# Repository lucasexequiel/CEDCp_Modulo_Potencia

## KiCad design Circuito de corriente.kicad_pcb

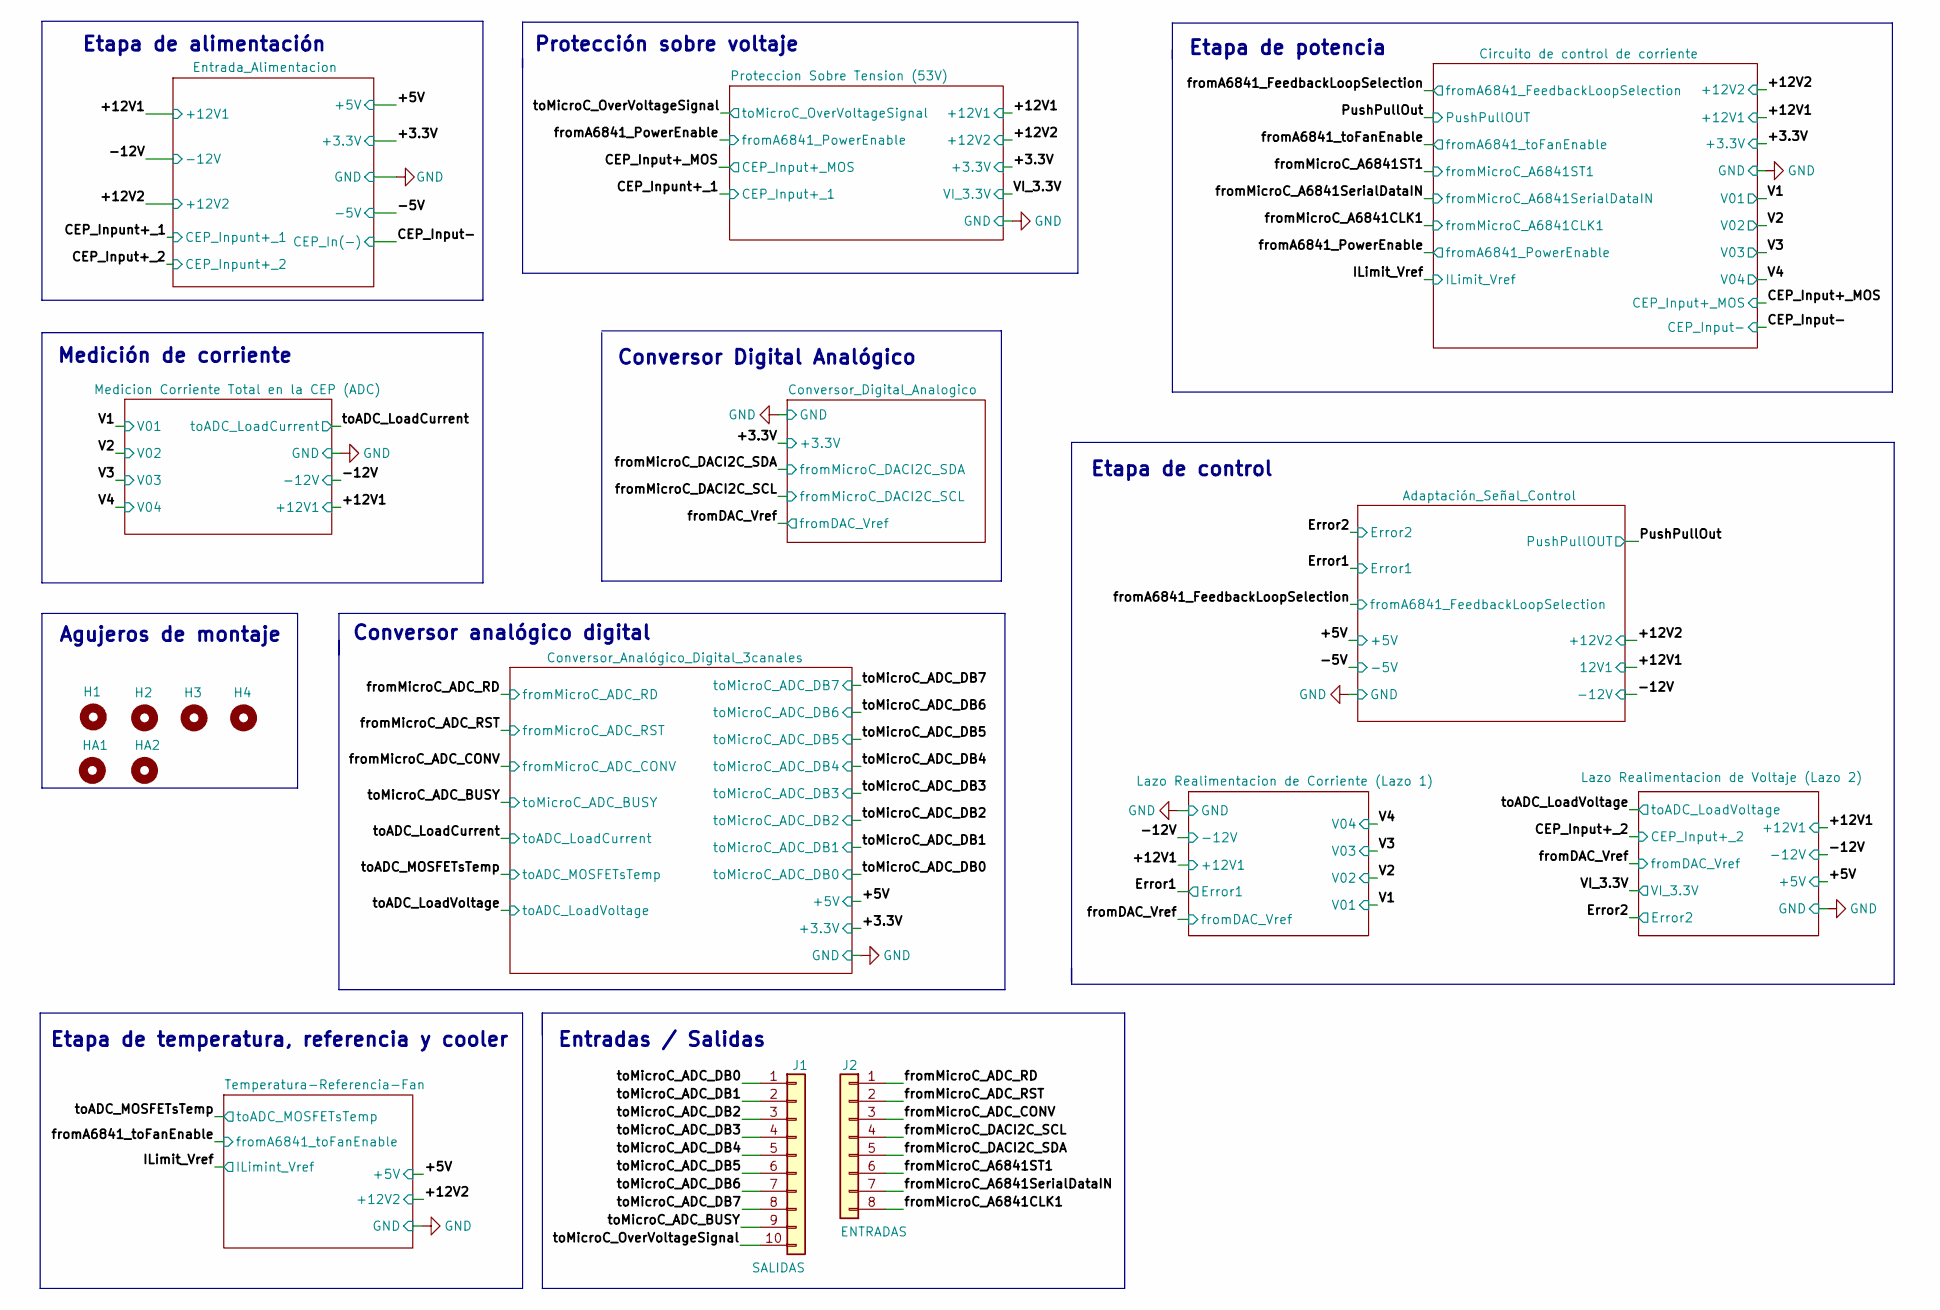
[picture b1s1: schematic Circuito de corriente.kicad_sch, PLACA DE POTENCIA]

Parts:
H1, H2, H3, H4: MountingHole; MountingHole_2.2mm_M2_Pad_Via
HA1, HA2: MountingHole; MountingHole_2.2mm_M2_Pad_Via
J1: SALIDAS; PinHeader_1x10_P2.54mm_Vertical
J2: ENTRADAS; PinHeader_1x08_P2.54mm_Vertical

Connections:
/fromMicroC_A6841CLK1: J2.8; also elsewhere on the board
/fromMicroC_A6841ST1: J2.6; also elsewhere on the board
/fromMicroC_A6841SerialDataIN: J2.7; also elsewhere on the board
/fromMicroC_ADC_CONV: J2.3; also elsewhere on the board
/fromMicroC_ADC_RD: J2.1; also elsewhere on the board
/fromMicroC_ADC_RST: J2.2; also elsewhere on the board
/fromMicroC_DACI2C_SCL: J2.4; also elsewhere on the board
/fromMicroC_DACI2C_SDA: J2.5; also elsewhere on the board
/toMicroC_ADC_BUSY: J1.9; also elsewhere on the board
/toMicroC_ADC_DB0: J1.1; also elsewhere on the board
/toMicroC_ADC_DB1: J1.2; also elsewhere on the board
/toMicroC_ADC_DB2: J1.3; also elsewhere on the board
/toMicroC_ADC_DB3: J1.4; also elsewhere on the board
/toMicroC_ADC_DB4: J1.5; also elsewhere on the board
/toMicroC_ADC_DB5: J1.6; also elsewhere on the board
/toMicroC_ADC_DB6: J1.7; also elsewhere on the board
/toMicroC_ADC_DB7: J1.8; also elsewhere on the board
/toMicroC_OverVoltageSignal: J1.10; also elsewhere on the board

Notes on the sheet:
Etapa de control
Agujeros de montaje
Etapa de temperatura, referencia y cooler
Protección sobre voltaje
Conversor Digital Analógico
Entradas / Salidas
Conversor analógico digital
Medición de corriente
Etapa de potencia
Etapa de alimentación

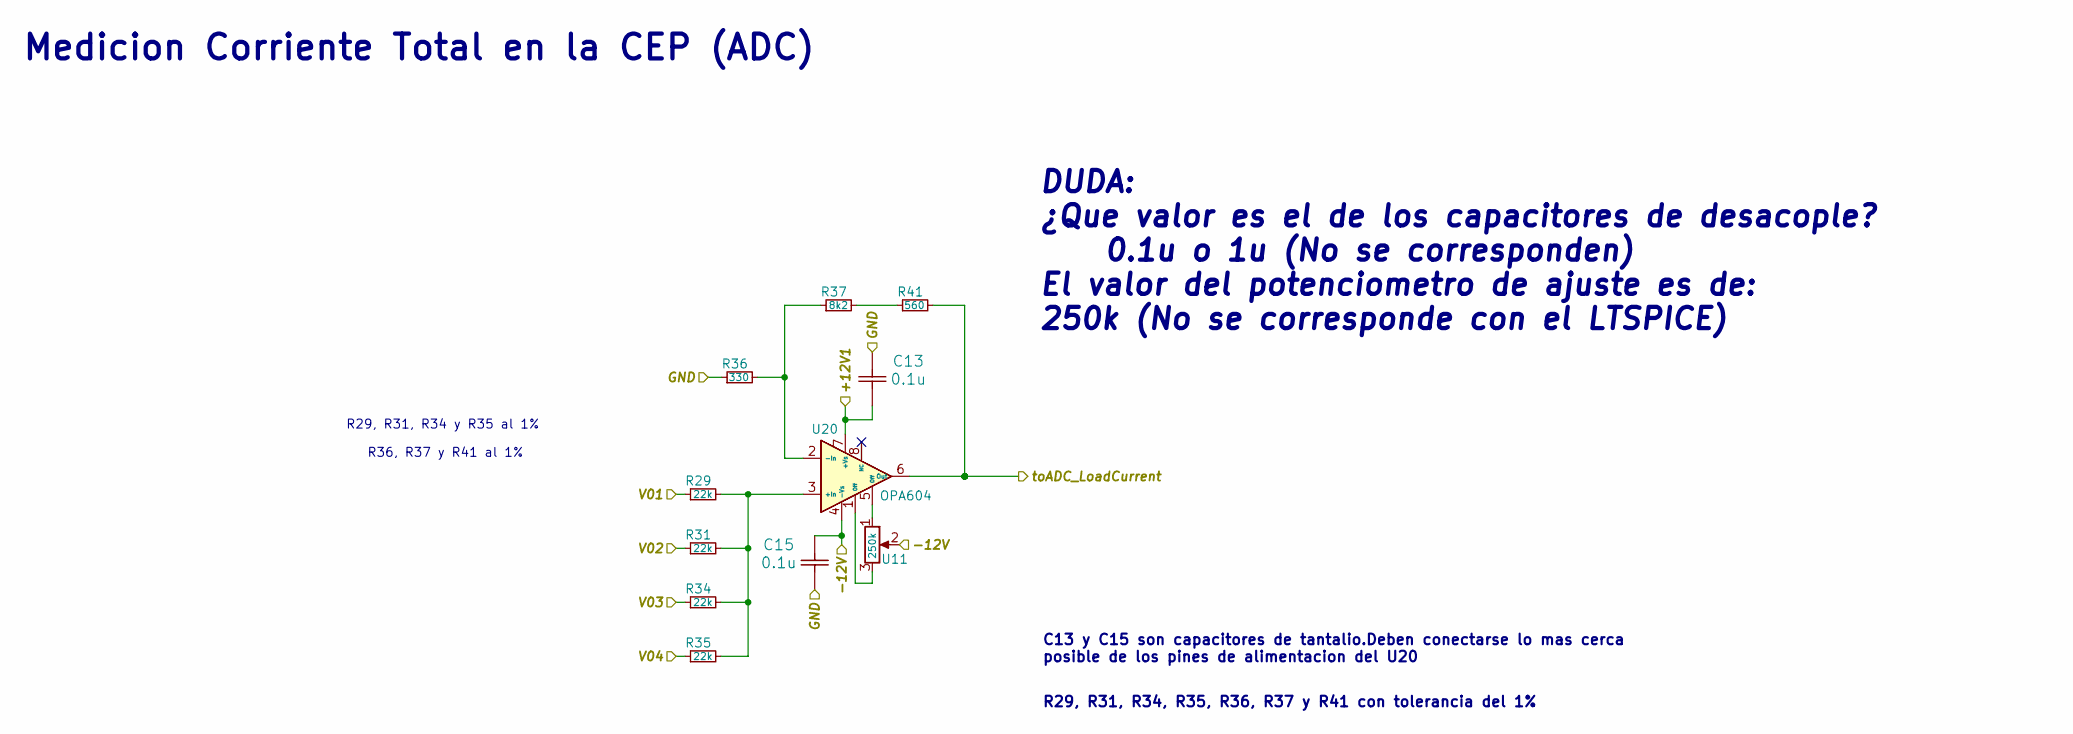
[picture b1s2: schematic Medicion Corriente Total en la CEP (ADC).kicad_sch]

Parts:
C13, C15: 0.1u; C_Disc_D7.5mm_W2.5mm_P5.00mm
R29, R31, R34, R35: 22k; Resistencia_0,25W
R36: 330; Resistencia_0,25W
R37: 8k2; Resistencia_0,25W
R41: 560; Resistencia_0,25W
U11: 250k; Preset_Multivueltas_Vertical
U20: OPA604

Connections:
/+12V1: C13.2, U20.7 (+Vs); also elsewhere on the board
/V1: R29.1; also elsewhere on the board
/V2: R31.1; also elsewhere on the board
/V3: R34.1; also elsewhere on the board
/V4: R35.1; also elsewhere on the board
/toADC_LoadCurrent: R41.2, U20.6 (Out); also elsewhere on the board
GND: C13.1, C15.2, R36.1; also elsewhere on the board
unnamed: R29.2, R31.2, R34.2, R35.2, U20.3 (+In)
unnamed: R36.2, R37.1, U20.2 (-In)
unnamed: R37.2, R41.1

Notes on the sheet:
R29, R31, R34, R35, R36, R37 y R41 con tolerancia del 1%
DUDA: ¿Que valor es el de los capacitores de desacople? 0.1u o 1u (No se corresponden) El valor del potenciometro de ajuste es de: 250k (No se corresponde con el LTSPICE)
R36, R37 y R41 al 1%
Medicion Corriente Total en la CEP (ADC)
C13 y C15 son capacitores de tantalio.Deben conectarse lo mas cerca posible de los pines de alimentacion del U20
R29, R31, R34 y R35 al 1%

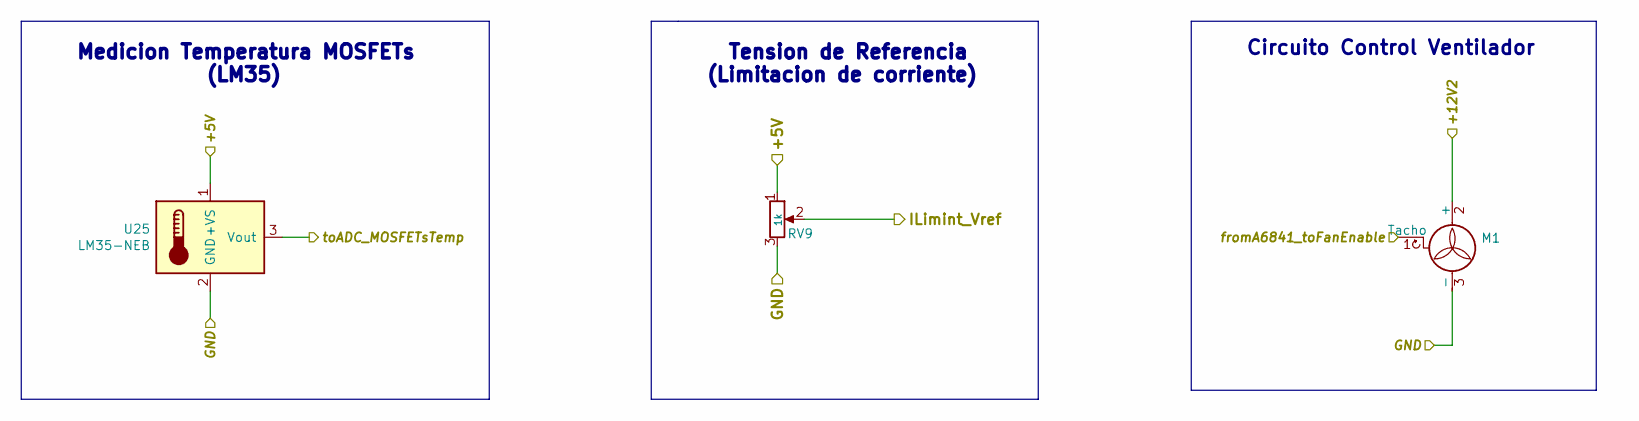
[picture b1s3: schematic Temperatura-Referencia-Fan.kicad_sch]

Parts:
M1: Fan_3pin; PinHeader_1x03_P2.54mm_Vertical
RV9: 1k; Preset_Multivueltas_Vertical
U25: LM35-NEB; PinHeader_1x03_P2.54mm_Vertical

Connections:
/+5V: RV9.1, U25.1 (+VS); also elsewhere on the board
/+12V2: M1.2 (+); also elsewhere on the board
/ILimit_Vref: RV9.2; also elsewhere on the board
/fromA6841_toFanEnable: M1.1 (Tacho); also elsewhere on the board
/toADC_MOSFETsTemp: U25.3 (Vout); also elsewhere on the board
GND: M1.3 (-), RV9.3, U25.2 (GND); also elsewhere on the board

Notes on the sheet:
Tension de Referencia (Limitacion de corriente)
Medicion Temperatura MOSFETs (LM35)
Circuito Control Ventilador

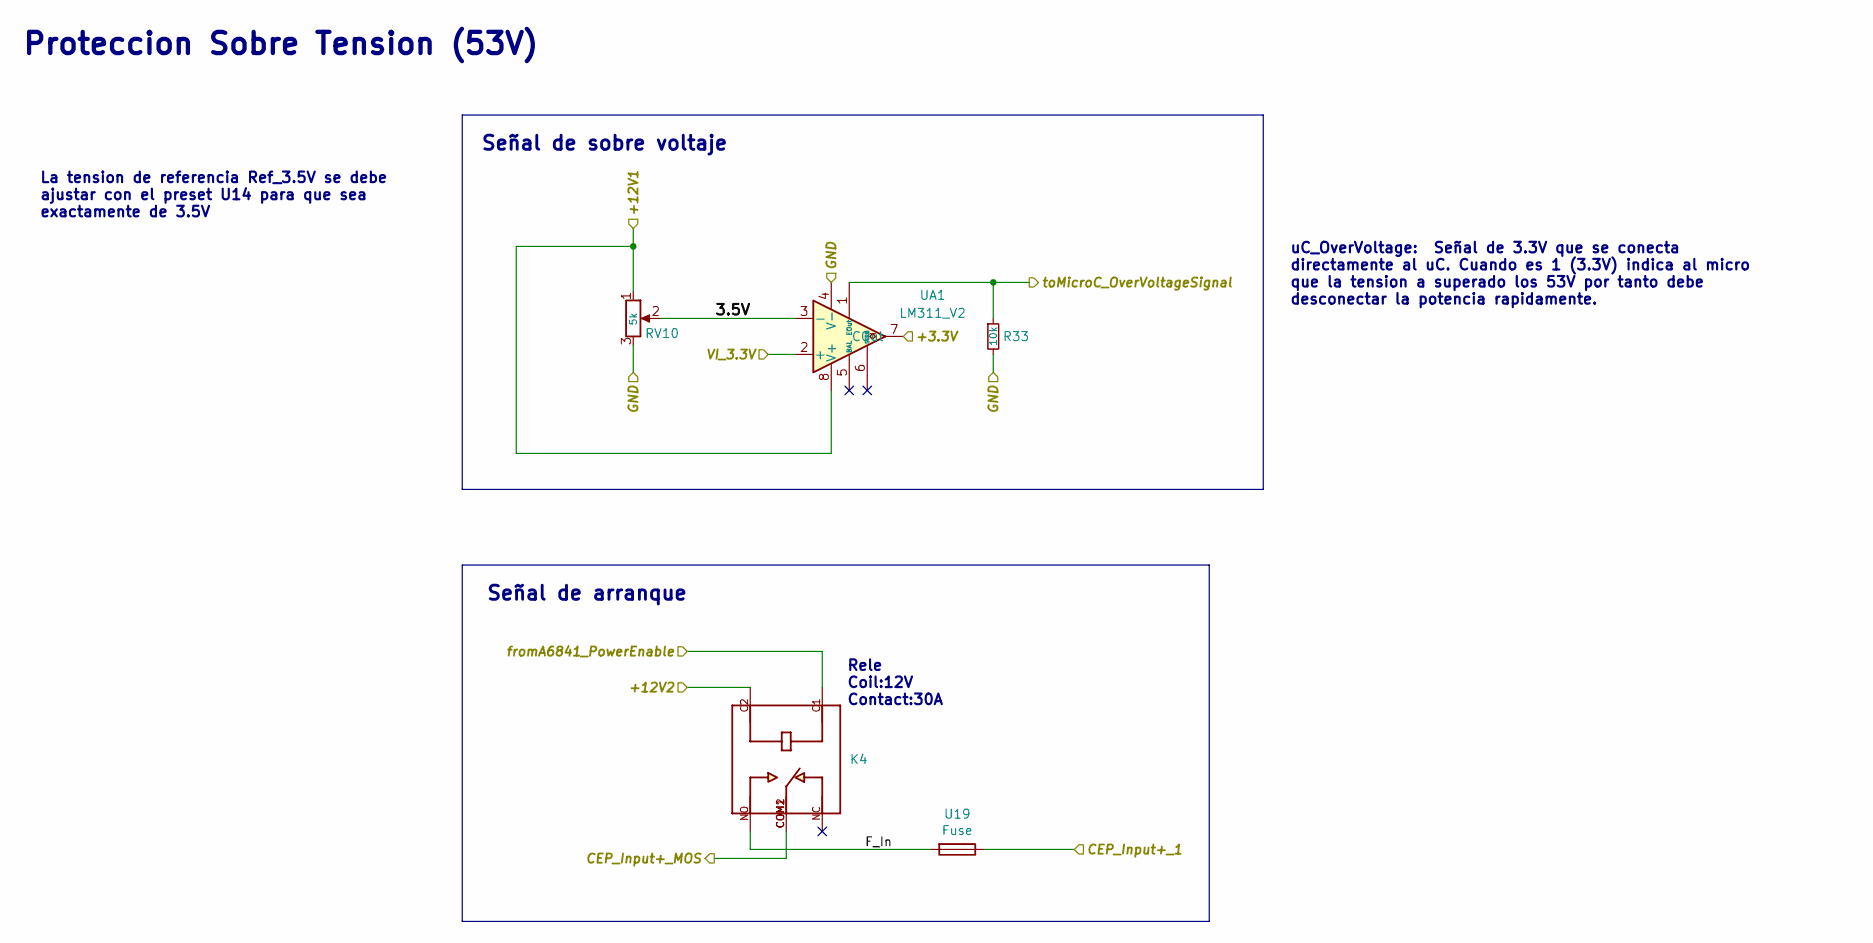
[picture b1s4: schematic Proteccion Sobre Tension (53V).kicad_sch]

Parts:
K4: SLA-12VDC-SL-C; RELE_30A
R33: 10k; Resistencia_0,25W
RV10: 5k; Preset_Multivueltas_Vertical
U19: Fuse
UA1: LM311_V2

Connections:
/+3.3V: UA1.7 (COut); also elsewhere on the board
/+12V1: RV10.1, UA1.8 (V+); also elsewhere on the board
/+12V2: K4.C2; also elsewhere on the board
/CEP_Inpunt+_1: U19.1; also elsewhere on the board
/CEP_Input+_MOS: K4.COM1, K4.COM2; also elsewhere on the board
/Proteccion Sobre Tension (53V)/3.5V: RV10.2, UA1.3 (-)
/Proteccion Sobre Tension (53V)/F_In: K4.NO, U19.2
/VI_3.3V: UA1.2 (+); also elsewhere on the board
/fromA6841_PowerEnable: K4.C1; also elsewhere on the board
/toMicroC_OverVoltageSignal: R33.1, UA1.1 (EOut); also elsewhere on the board
GND: R33.2, RV10.3, UA1.4 (V-); also elsewhere on the board

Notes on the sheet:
Señal de arranque
La tension de referencia Ref_3.5V se debe ajustar con el preset U14 para que sea exactamente de 3.5V
Rele Coil:12V Contact:30A
Proteccion Sobre Tension (53V)
uC_OverVoltage: Señal de 3.3V que se conecta directamente al uC. Cuando es 1 (3.3V) indica al micro que la tension a superado los 53V por tanto debe desconectar la potencia rapidamente.
Señal de sobre voltaje

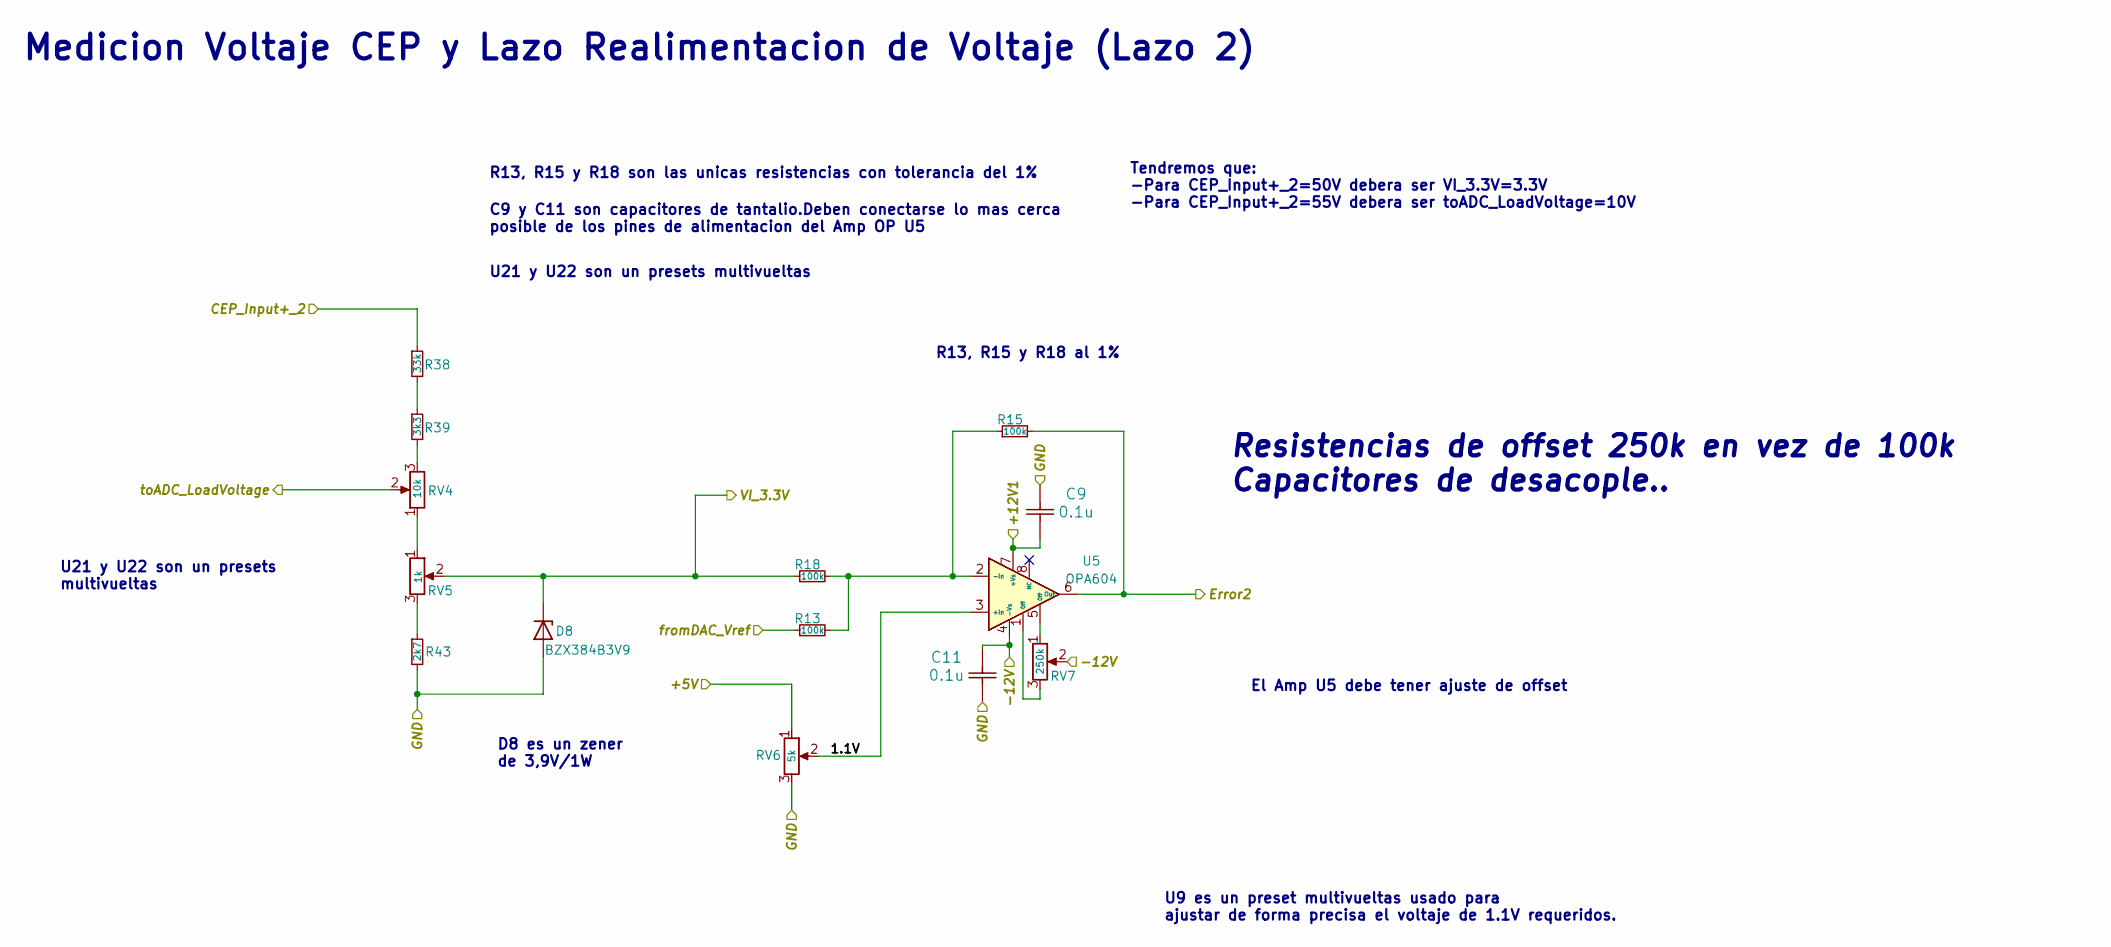
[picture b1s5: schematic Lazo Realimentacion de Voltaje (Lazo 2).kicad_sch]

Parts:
C9, C11: 0.1u; C_Disc_D7.5mm_W2.5mm_P5.00mm
D8: BZX384B3V9; D_DO-15_P10.16mm_Horizontal
R13, R15, R18: 100k; Resistencia_0,25W
R38: 33k; Resistencia_0,25W
R39: 3k3; Resistencia_0,25W
R43: 2k7; Resistencia_0,25W
RV4: 10k; Preset_Multivueltas_Vertical
RV5: 1k; Preset_Multivueltas_Vertical
RV6: 5k; Preset_Multivueltas_Vertical
RV7: 250k; Preset_Multivueltas_Vertical
U5: OPA604

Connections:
/+5V: RV6.1; also elsewhere on the board
/+12V1: C9.2, U5.7 (+Vs); also elsewhere on the board
/CEP_Input+_2: R38.1; also elsewhere on the board
/Error2: R15.2, U5.6 (Out); also elsewhere on the board
/Lazo Realimentacion de Voltaje (Lazo 2)/1.1V: RV6.2, U5.3 (+In)
/VI_3.3V: D8.1 (K), R18.1, RV5.2; also elsewhere on the board
/fromDAC_Vref: R13.1; also elsewhere on the board
/toADC_LoadVoltage: RV4.2; also elsewhere on the board
GND: C9.1, C11.1, D8.2 (A), R43.2, RV6.3; also elsewhere on the board
unnamed: R13.2, R15.1, R18.2, U5.2 (-In)
unnamed: R38.2, R39.1
unnamed: R39.2, RV4.3
unnamed: R43.1, RV5.3
unnamed: RV4.1, RV5.1
unnamed: RV7.1, U5.5 (Off)
unnamed: RV7.3, U5.1 (Off)

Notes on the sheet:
U9 es un preset multivueltas usado para ajustar de forma precisa el voltaje de 1.1V requeridos.
C9 y C11 son capacitores de tantalio.Deben conectarse lo mas cerca posible de los pines de alimentacion del Amp OP U5
El Amp U5 debe tener ajuste de offset
U21 y U22 son un presets multivueltas
D8 es un zener de 3,9V/1W
R13, R15 y R18 al 1%
Resistencias de offset 250k en vez de 100k Capacitores de desacople..
U21 y U22 son un presets multivueltas
Medicion Voltaje CEP y Lazo Realimentacion de Voltaje (Lazo 2)
Tendremos que: -Para CEP_Input+_2=50V debera ser VI_3.3V=3.3V -Para CEP_Input+_2=55V debera ser toADC_LoadVoltage=10V
R13, R15 y R18 son las unicas resistencias con tolerancia del 1%

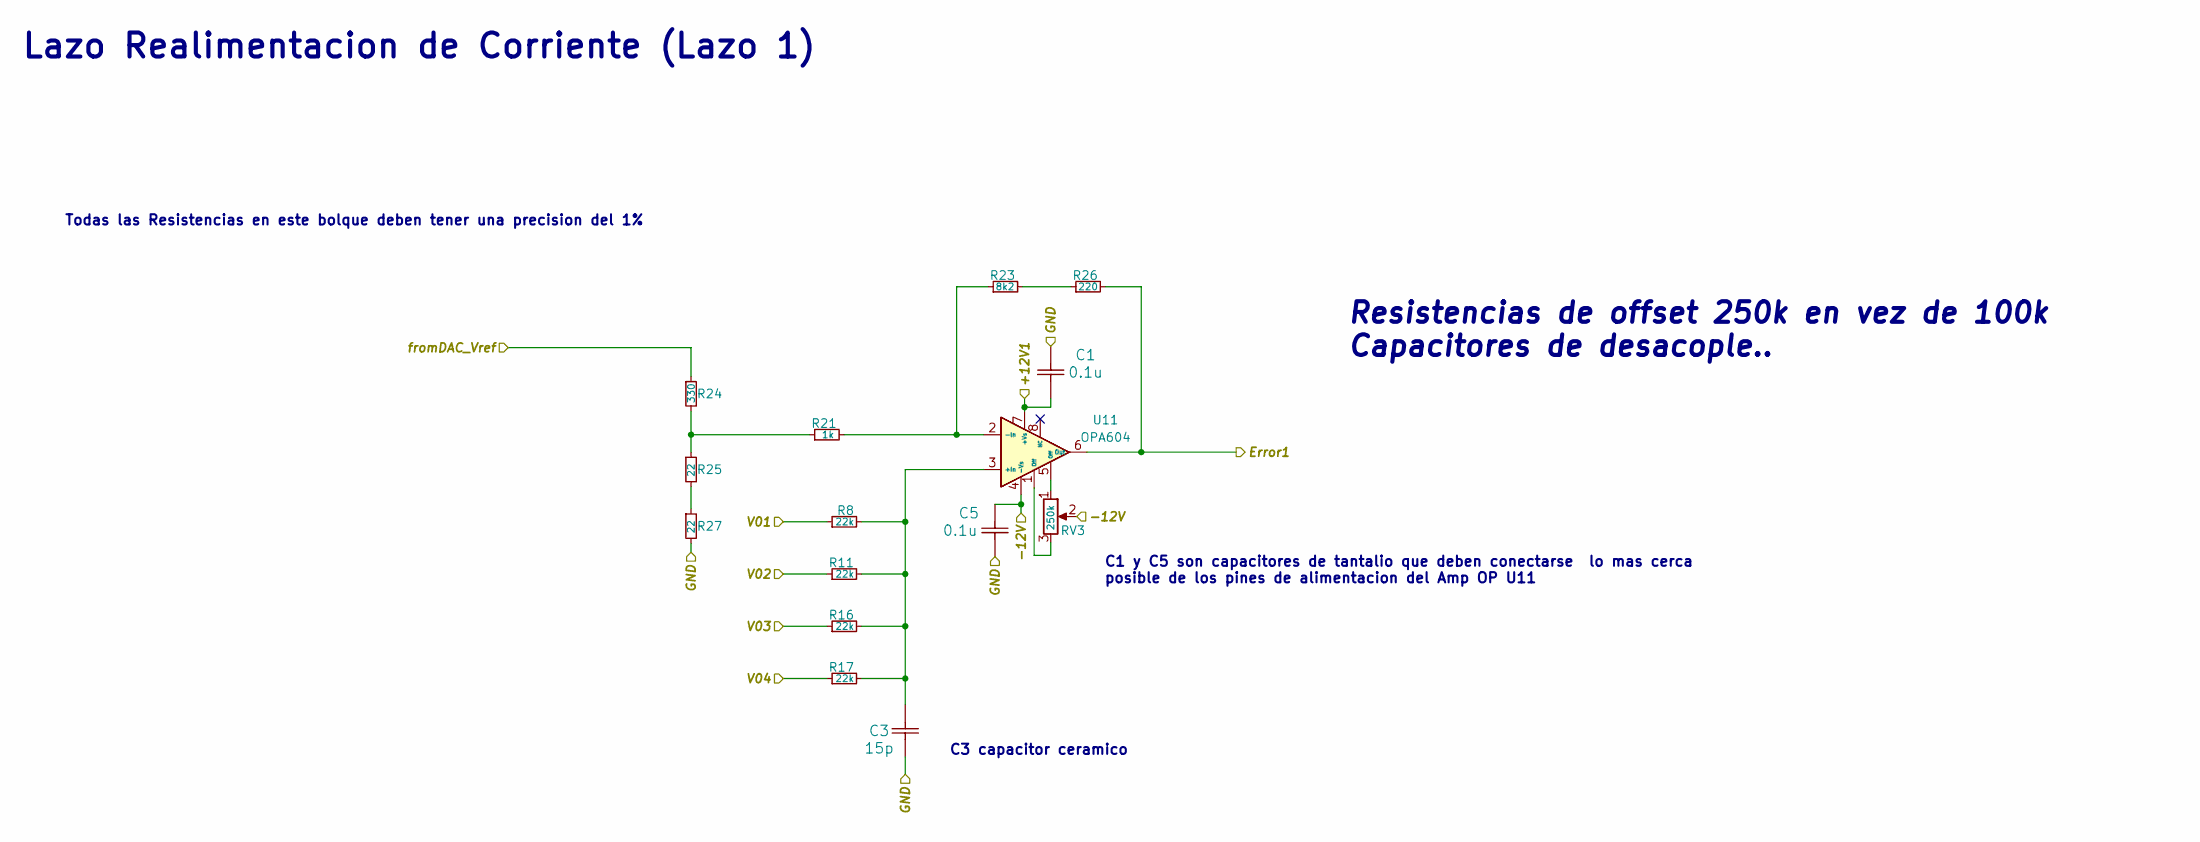
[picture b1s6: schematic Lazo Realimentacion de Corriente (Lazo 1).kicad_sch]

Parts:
C1, C5: 0.1u; C_Disc_D7.5mm_W2.5mm_P5.00mm
C3: 15p; C_Disc_D7.5mm_W2.5mm_P5.00mm
R8, R11, R16, R17: 22k; Resistencia_0,25W
R21: 1k; Resistencia_0,25W
R23: 8k2; Resistencia_0,25W
R24: 330; Resistencia_0,25W
R25, R27: 22; Resistencia_0,25W
R26: 220; Resistencia_0,25W
RV3: 250k; Preset_Multivueltas_Vertical
U11: OPA604

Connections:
/+12V1: C1.2, U11.7 (+Vs); also elsewhere on the board
/Error1: R26.2, U11.6 (Out); also elsewhere on the board
/V1: R8.1; also elsewhere on the board
/V2: R11.1; also elsewhere on the board
/V3: R16.1; also elsewhere on the board
/V4: R17.1; also elsewhere on the board
/fromDAC_Vref: R24.1; also elsewhere on the board
GND: C1.1, C3.1, C5.2, R27.2; also elsewhere on the board
unnamed: R21.1, R24.2, R25.1
unnamed: R23.2, R26.1
unnamed: R25.2, R27.1
unnamed: RV3.1, U11.5 (Off)

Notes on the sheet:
C3 capacitor ceramico
Resistencias de offset 250k en vez de 100k Capacitores de desacople..
Lazo Realimentacion de Corriente (Lazo 1)
Todas las Resistencias en este bolque deben tener una precision del 1%
C1 y C5 son capacitores de tantalio que deben conectarse lo mas cerca posible de los pines de alimentacion del Amp OP U11

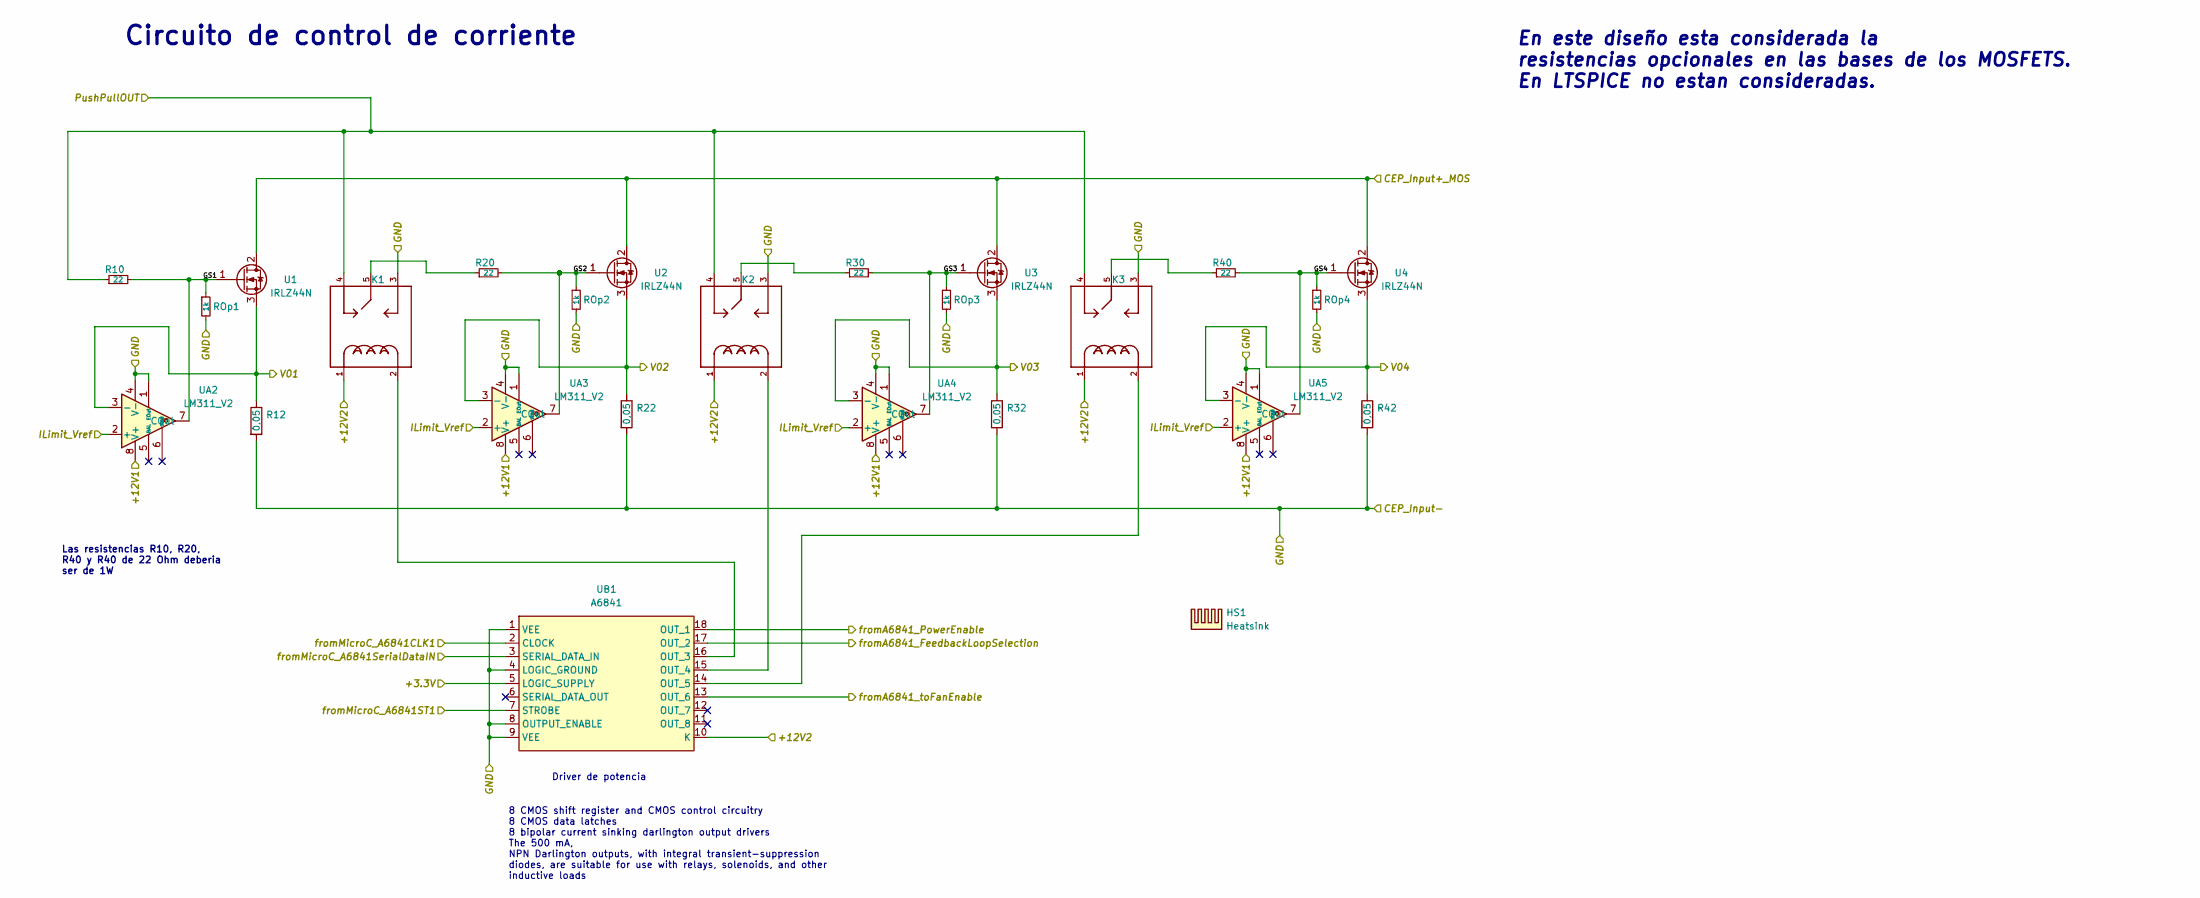
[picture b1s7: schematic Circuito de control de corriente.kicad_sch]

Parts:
HS1: Heatsink; Heatsink_125x35x50mm_3xFixationM3
K1, K2, K3: JJM1-12V; RELAY_JJM1-12V
R10, R20, R30, R40: 22; Resistencia_0,25W
R12, R22, R32, R42: 0,05; C_Rect_L16.5mm_W4.7mm_P15.00mm_MKT
ROp1, ROp2, ROp3, ROp4: 1k; Resistencia_0,25W
U1, U2, U3, U4: IRLZ44N; TO-220-3_Vertical
UA2, UA3, UA4, UA5: LM311_V2
UB1: A6841

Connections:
/+3.3V: UB1.5 (LOGIC_SUPPLY); also elsewhere on the board
/+12V1: UA2.8 (V+), UA3.8 (V+), UA4.8 (V+), UA5.8 (V+); also elsewhere on the board
/+12V2: K1.1, K2.1, K3.1, UB1.10 (K); also elsewhere on the board
/CEP_Input+_MOS: U1.2 (D), U2.2 (D), U3.2 (D), U4.2 (D); also elsewhere on the board
/Circuito de control de corriente/GS1: R10.2, ROp1.1, U1.1 (G), UA2.7 (COut)
/Circuito de control de corriente/GS2: R20.2, ROp2.1, U2.1 (G), UA3.7 (COut)
/Circuito de control de corriente/GS3: R30.2, ROp3.1, U3.1 (G), UA4.7 (COut)
/Circuito de control de corriente/GS4: R40.2, ROp4.1, U4.1 (G), UA5.7 (COut)
/ILimit_Vref: UA2.2 (+), UA3.2 (+), UA4.2 (+), UA5.2 (+); also elsewhere on the board
/PushPullOut: K1.4 (NC), K2.4 (NC), K3.4 (NC), R10.1; also elsewhere on the board
/V1: R12.1, U1.3 (S), UA2.3 (-); also elsewhere on the board
/V2: R22.1, U2.3 (S), UA3.3 (-); also elsewhere on the board
/V3: R32.1, U3.3 (S), UA4.3 (-); also elsewhere on the board
/V4: R42.1, U4.3 (S), UA5.3 (-); also elsewhere on the board
/fromA6841_FeedbackLoopSelection: UB1.17 (OUT_2); also elsewhere on the board
/fromA6841_PowerEnable: UB1.18 (OUT_1); also elsewhere on the board
/fromA6841_toFanEnable: UB1.13 (OUT_6); also elsewhere on the board
/fromMicroC_A6841CLK1: UB1.2 (CLOCK); also elsewhere on the board
/fromMicroC_A6841ST1: UB1.7 (STROBE); also elsewhere on the board
/fromMicroC_A6841SerialDataIN: UB1.3 (SERIAL_DATA_IN); also elsewhere on the board
GND: K1.3 (NO), K2.3 (NO), K3.3 (NO), R12.2, R22.2, R32.2, R42.2, ROp1.2, ROp2.2, ROp3.2, ROp4.2, UA2.1 (EOut), UA2.4 (V-), UA3.1 (EOut), UA3.4 (V-), UA4.1 (EOut), UA4.4 (V-), UA5.1 (EOut), UA5.4 (V-), UB1.1 (VEE), UB1.4 (LOGIC_GROUND), UB1.8 (OUTPUT_ENABLE), UB1.9 (VEE); also elsewhere on the board
unnamed: K1.2, UB1.16 (OUT_3)
unnamed: K1.5 (C), R20.1
unnamed: K2.2, UB1.15 (OUT_4)
unnamed: K2.5 (C), R30.1
unnamed: K3.2, UB1.14 (OUT_5)
unnamed: K3.5 (C), R40.1

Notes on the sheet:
Driver de potencia
8 CMOS shift register and CMOS control circuitry 8 CMOS data latches 8 bipolar current sinking darlington output drivers The 500 mA, NPN Darlington outputs, with integral transient-suppression diodes, are suitable for use with relays, solenoids, and other inductive loads
Circuito de control de corriente
Las resistencias R10, R20, R40 y R40 de 22 Ohm deberia ser de 1W
En este diseño esta considerada la resistencias opcionales en las bases de los MOSFETS. En LTSPICE no estan consideradas.

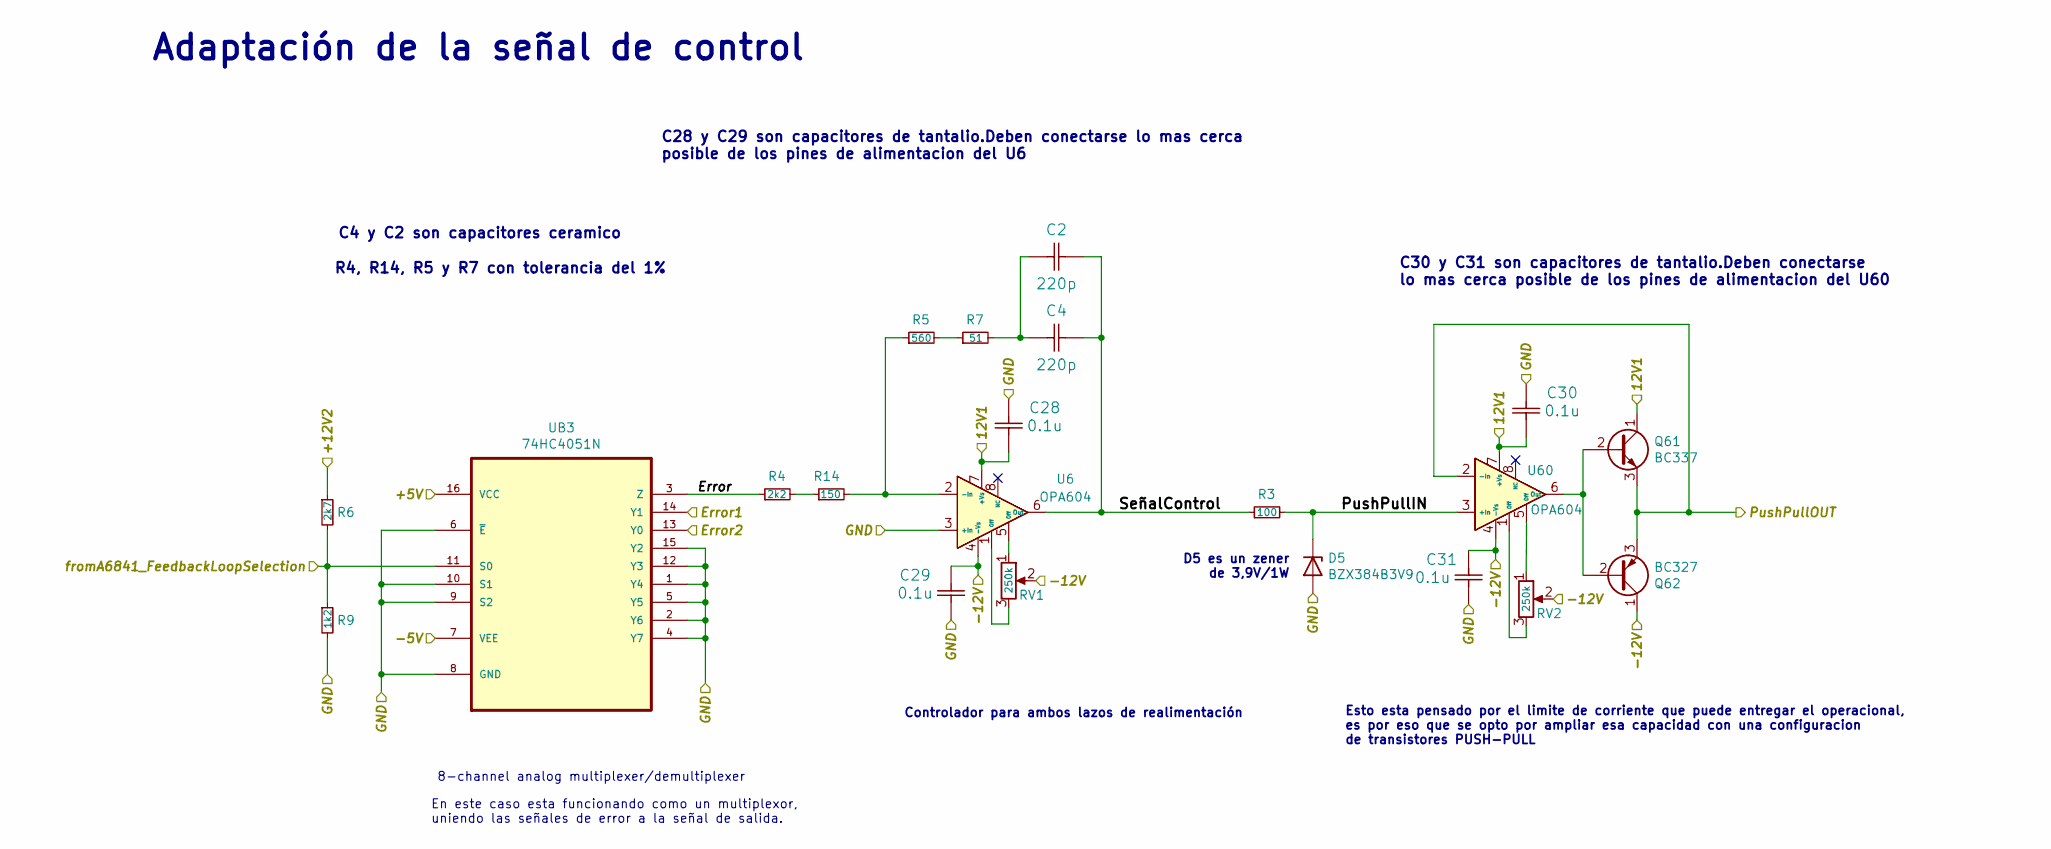
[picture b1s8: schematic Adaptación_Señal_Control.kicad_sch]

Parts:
C2, C4: 220p; C_Disc_D7.5mm_W2.5mm_P5.00mm
C28, C29, C30, C31: 0.1u; C_Disc_D7.5mm_W2.5mm_P5.00mm
D5: BZX384B3V9; D_DO-41_SOD81_P10.16mm_Horizontal
Q61: BC337; TO-92_Inline
Q62: BC327; TO-92_Inline
R3: 100; Resistencia_0,25W
R4: 2k2; Resistencia_0,25W
R5: 560; Resistencia_0,25W
R6: 2k7; Resistencia_0,25W
R7: 51; Resistencia_0,25W
R9: 1k2; Resistencia_0,25W
R14: 150; Resistencia_0,25W
RV1, RV2: 250k; Preset_Multivueltas_Vertical
U6, U60: OPA604
UB3: 74HC4051N; 74HC4051M; MPN 74HC4051N,652

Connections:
/+5V: UB3.16 (VCC); also elsewhere on the board
/+12V1: C28.2, C30.2, Q61.1 (C), U6.7 (+Vs), U60.7 (+Vs); also elsewhere on the board
/+12V2: R6.1; also elsewhere on the board
/-5V: UB3.7 (VEE); also elsewhere on the board
/Adaptación_Señal_Control/Error: R4.1, UB3.3 (Z)
/Adaptación_Señal_Control/PushPullIN: D5.1 (K), R3.2, U60.3 (+In)
/Adaptación_Señal_Control/SeñalControl: C2.1, C4.1, R3.1, U6.6 (Out)
/Error1: UB3.14 (Y1); also elsewhere on the board
/Error2: UB3.13 (Y0); also elsewhere on the board
/PushPullOut: Q61.3 (E), Q62.3 (E), U60.2 (-In); also elsewhere on the board
/fromA6841_FeedbackLoopSelection: R6.2, R9.1, UB3.11 (S0); also elsewhere on the board
GND: C28.1, C29.2, C30.1, C31.2, D5.2 (A), R9.2, U6.3 (+In), UB3.1 (Y4), UB3.2 (Y6), UB3.4 (Y7), UB3.5 (Y5), UB3.6 (~E), UB3.8 (GND), UB3.9 (S2), UB3.10 (S1), UB3.12 (Y3), UB3.15 (Y2); also elsewhere on the board
unnamed: C2.2, C4.2, R7.2
unnamed: Q61.2 (B), Q62.2 (B), U60.6 (Out)
unnamed: R5.2, R7.1
unnamed: R4.2, R14.1
unnamed: R5.1, R14.2, U6.2 (-In)
unnamed: RV1.1, U6.5 (Off)
unnamed: RV1.3, U6.1 (Off)
unnamed: RV2.1, U60.5 (Off)
unnamed: RV2.3, U60.1 (Off)

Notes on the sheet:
C28 y C29 son capacitores de tantalio.Deben conectarse lo mas cerca posible de los pines de alimentacion del U6
8-channel analog multiplexer/demultiplexer
R4, R14, R5 y R7 con tolerancia del 1%
C30 y C31 son capacitores de tantalio.Deben conectarse lo mas cerca posible de los pines de alimentacion del U60
D5 es un zener de 3,9V/1W
Adaptación de la señal de control
Esto esta pensado por el limite de corriente que puede entregar el operacional, es por eso que se opto por ampliar esa capacidad con una configuracion de transistores PUSH-PULL
Controlador para ambos lazos de realimentación
C4 y C2 son capacitores ceramico
En este caso esta funcionando como un multiplexor, uniendo las señales de error a la señal de salida.

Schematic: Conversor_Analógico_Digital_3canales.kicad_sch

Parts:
UB2: AD7606_M

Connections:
/+3.3V: UB2.7 (VIO), UB2.15 (DB14), UB2.16 (DB15), UB2.28 (RAGE); also elsewhere on the board
/+5V: UB2.1 (+5V); also elsewhere on the board
/fromMicroC_ADC_CONV: UB2.4 (CVA), UB2.27 (CVB); also elsewhere on the board
/fromMicroC_ADC_RD: UB2.26 (RD); also elsewhere on the board
/fromMicroC_ADC_RST: UB2.5 (RST); also elsewhere on the board
/toADC_LoadCurrent: UB2.39 (V1); also elsewhere on the board
/toADC_LoadVoltage: UB2.40 (V2); also elsewhere on the board
/toADC_MOSFETsTemp: UB2.41 (V3); also elsewhere on the board
/toMicroC_ADC_BUSY: UB2.25 (BUSY); also elsewhere on the board
/toMicroC_ADC_DB0: UB2.8 (DB0); also elsewhere on the board
/toMicroC_ADC_DB1: UB2.23 (DB1); also elsewhere on the board
/toMicroC_ADC_DB2: UB2.9 (DB2); also elsewhere on the board
/toMicroC_ADC_DB3: UB2.22 (DB3); also elsewhere on the board
/toMicroC_ADC_DB4: UB2.10 (DB4); also elsewhere on the board
/toMicroC_ADC_DB5: UB2.21 (DB5); also elsewhere on the board
/toMicroC_ADC_DB6: UB2.11 (DB6); also elsewhere on the board
/toMicroC_ADC_DB7: UB2.20 (DB7); also elsewhere on the board
GND: UB2.2 (OS0), UB2.3 (OS2), UB2.6 (CS), UB2.29 (OS1), UB2.30 (GND), UB2.31 (GND_8), UB2.32 (GND_7), UB2.33 (GND_6), UB2.34 (GND_5), UB2.35 (GND_4), UB2.36 (GND_3), UB2.37 (GND_2), UB2.38 (GND_1), UB2.42 (V4), UB2.43 (V5), UB2.44 (V6), UB2.45 (V7), UB2.46 (V8); also elsewhere on the board

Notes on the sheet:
IMPORTANTE: Hay que mover la resistencia ubicada en la posicion R2 de la placa del ADC a la posicion R1 para habilitar el modo paralelo Byte
Conversor Analogico a Digital (3 canales)

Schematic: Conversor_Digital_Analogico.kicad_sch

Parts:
C6: 0.1u; C_Disc_D7.5mm_W2.5mm_P5.00mm
C7: 10u; CP_Radial_D4.0mm_P2.00mm
U26: MCP4725_Placa

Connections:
/+3.3V: C6.1, C7.1, U26.5 (VCC); also elsewhere on the board
/fromDAC_Vref: U26.1 (VOUT); also elsewhere on the board
/fromMicroC_DACI2C_SCL: U26.3 (SCL); also elsewhere on the board
/fromMicroC_DACI2C_SDA: U26.4 (SDA); also elsewhere on the board
GND: C6.2, C7.2, U26.2 (GND), U26.6 (GND); also elsewhere on the board

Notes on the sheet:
A0= debera conectarse a masa o 3.3V segun la direccion I2C que se le asisgne al DAC en el bus de comunicacion I2C
C6 y C7 se deben conectar lo mas cercano posible al pin Vdd del DAC para filtrar ruidos de la alimentacion que afectan la performance del DAC C6: Capacitor Ceramico C7: Capacitor Tantalio
Conversor Digital a Analogico (Vref)

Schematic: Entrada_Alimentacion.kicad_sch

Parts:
J3: +12V2; Bornera_1x2
J4: +3V3; Bornera_1x2
J5: +/- 5V; Bornera_1x3
J6: +/- 12V; Bornera_1x3
J11, J13: Conn_01x01; SolderWire-2sqmm_1x01_D2mm_OD3.9mm
J12, J14: Conn_01x01; SolderWire-0.5sqmm_1x01_D0.9mm_OD2.3mm

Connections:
/+3.3V: J4.1; also elsewhere on the board
/+5V: J5.3; also elsewhere on the board
/+12V1: J6.1; also elsewhere on the board
/+12V2: J3.2; also elsewhere on the board
/-5V: J5.1; also elsewhere on the board
/CEP_Inpunt+_1: J11.1; also elsewhere on the board
/CEP_Input+_2: J12.1; also elsewhere on the board
GND: J3.1, J4.2, J5.2, J6.2, J13.1, J14.1; also elsewhere on the board

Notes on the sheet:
Agregar bornera de medicion de voltaje
Alimentación
Entradas de tensión a la placa
Entrada CEDCp
AGREGAR TEST POINTS AGREGAR LEDS

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

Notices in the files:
Circuito de control de corriente.kicad_sch:
creativecommons.orgn/licenses/by/4.0
License: CC BY 4.0
Circuito de corriente.kicad_sch:
Licenses: CC BY 4.0
